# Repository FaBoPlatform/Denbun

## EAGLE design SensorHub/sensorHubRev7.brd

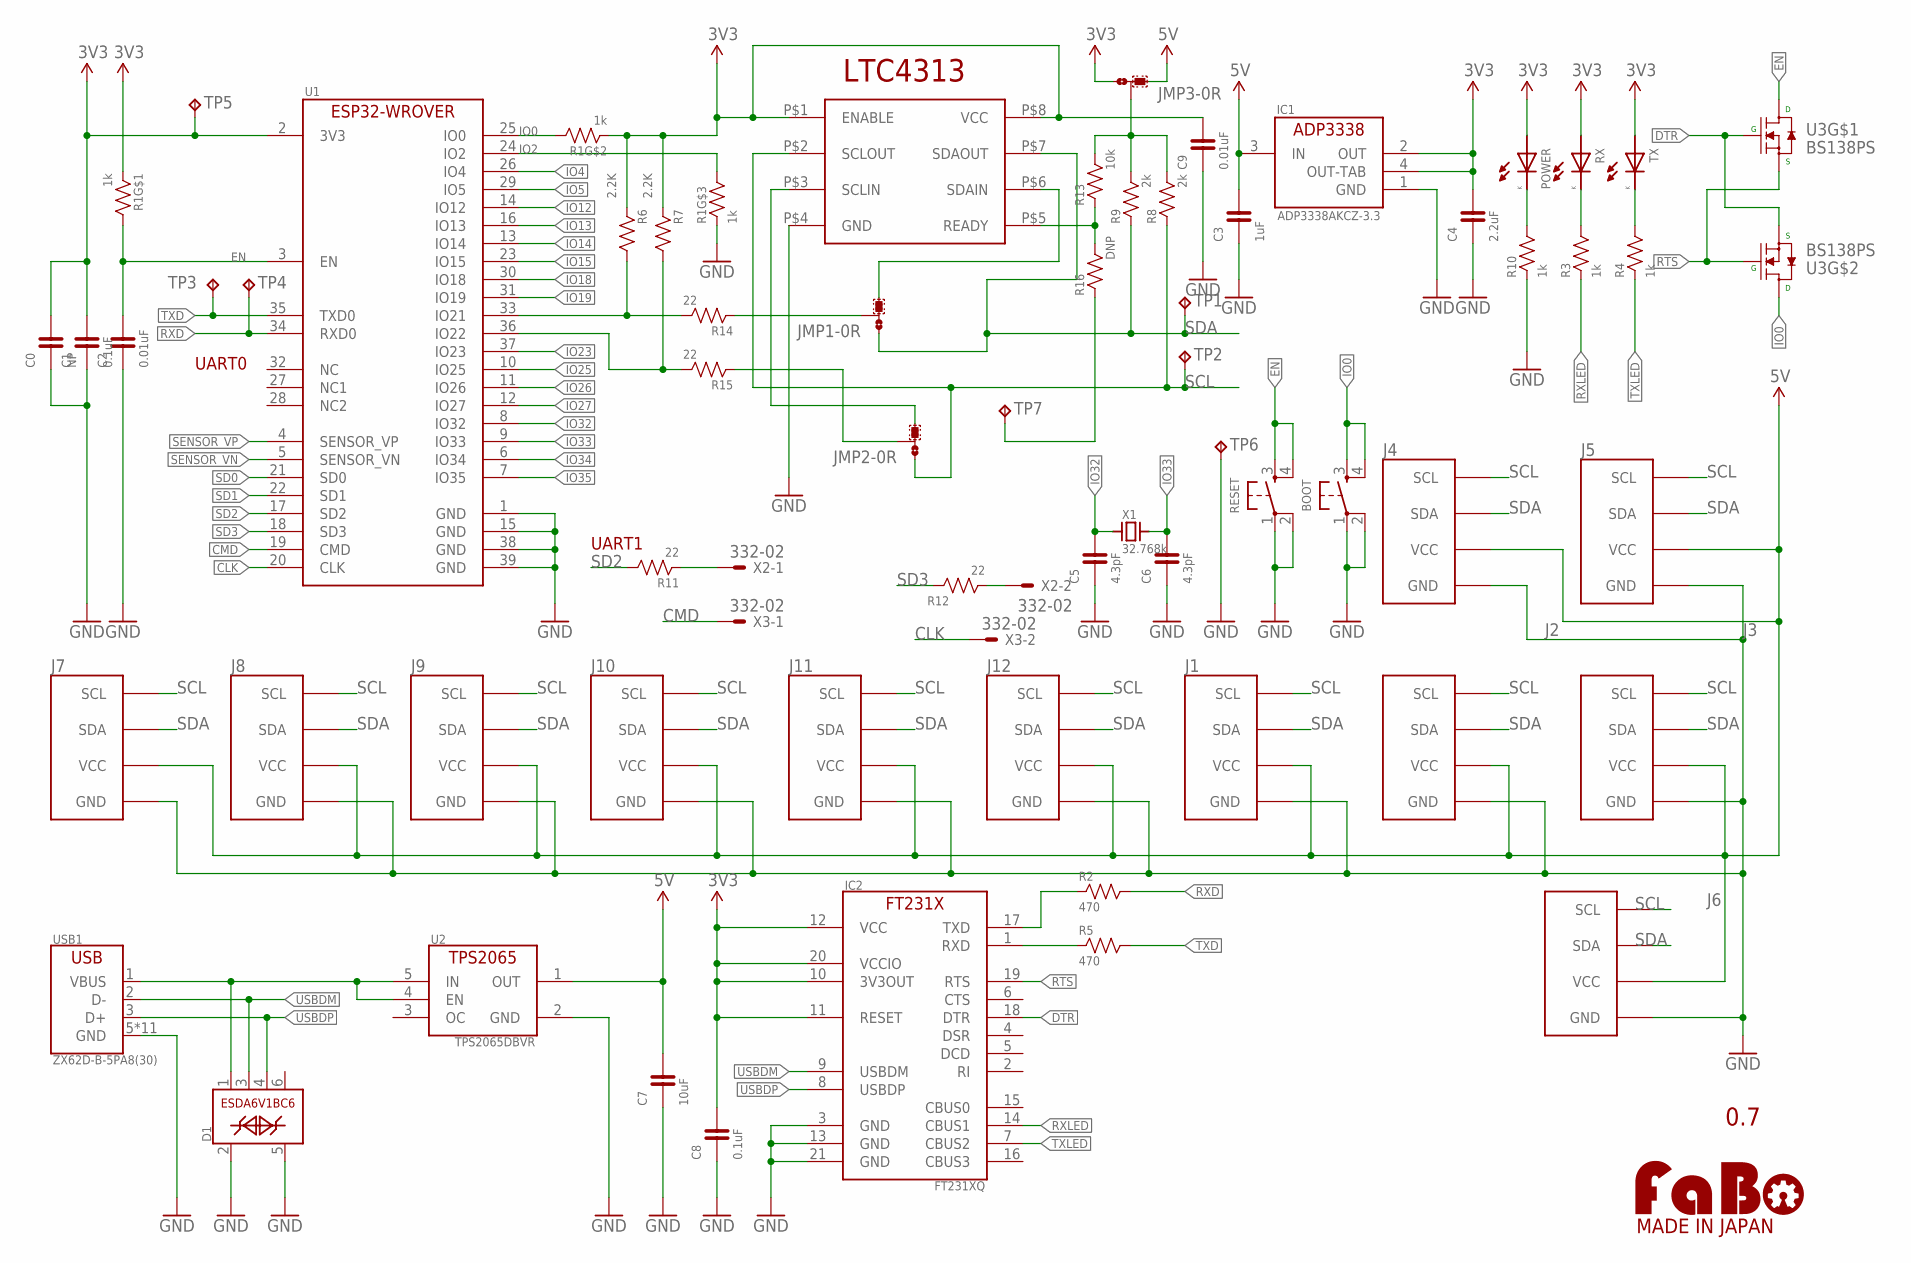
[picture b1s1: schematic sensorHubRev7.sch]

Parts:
BOOT: TACTILE-KMR2; KMR2-TACT
C0: NP; MULTIPAD0603
C1, C8: 0.1uF; EIA0603
C2, C9: 0.01uF; EIA0603
C3: 1uF; EIA0603
C4: 2.2uF; EIA0603
C5, C6: 4.3pF; EIA0603
C7: 10uF; EIA0603
D1: ESDA6V1BC6; SOT-23-6L
IC1: ADP3338AKCZ-3.3; SOT-223-KC3
IC2: FT231XQ; QFN-20
J1, J2, J3, J4, J5, J6, J7, J8, J9, J10, J11, J12: FABO_BRICK_I2C-S04B-PASK-2; FABO_BRICK_I2C_S04B-PASK-2
JMP1, JMP2: 0R-JUMPA; A0R-JMP
JMP3: 0R-JUMPB; B0R-JMP
LOGO1: LOGO_FABO-M_BOTTOM; LOGO_FABO_M_BOTTOM
POWER: LED-0603; LED_0603
R1: 1k; EXBV8V
R2, R5: 470; EIA0603
R3, R4, R10: 1k; EIA0603
R6, R7: 2.2K; EIA0603
R8, R9: 2k; EIA0603
R11, R12, R14, R15: 22; EIA0603
R13: 10k; EIA0603
R16: DNP; EIA0603
RESET: TACTILE-KMR2; KMR2-TACT
RX: LED-0603; LED_0603
TP1, TP2, TP3, TP4, TP5, TP6, TP7: TPB1,27; B1,27
TX: LED-0603; LED_0603
U1: ESP32-WROVER-B
U2: TPS2065DBVR; SOT-23-5
U3: BS138PS; SOT-363
U5: LTC4313
USB1: ZX62D-B-5PA8(30); ZX62D-B-5PA8
X1: 32.768k; ABS07
X2, X3: 332-02

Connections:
3V3: C0.2, C1.2, C4.2, C8.2, C9.2, IC1.2 (OUT), IC1.4 (OUT-TAB), IC2.10 (3V3OUT), IC2.11 (RESET), IC2.12 (VCC), IC2.20 (VCCIO), JMP3.3, POWER.A (ANODE), R1.1, R1.2 (1), R6.1, R7.1, RX.A (ANODE), TP5.TP, TX.A (ANODE), U1.2 (3V3), U5.P$1 (ENABLE), U5.P$8 (VCC)
5V: C3.2, C7.2, IC1.3 (IN), J1.VCC, J2.VCC, J3.VCC, J4.VCC, J5.VCC, J6.VCC, J7.VCC, J8.VCC, J9.VCC, J10.VCC, J11.VCC, J12.VCC, JMP3.1, U2.1 (OUT)
CLK: U1.20 (CLK), X3.2
CMD: U1.19 (CMD), X3.1
DTR: IC2.18 (DTR), U3.2 (G), U3.4 (S)
EN: C2.2, R1.8 (2), RESET.3, RESET.4, U1.3 (EN), U3.6 (D)
GND: BOOT.1, BOOT.2, C0.1, C1.1, C2.1, C3.1, C4.1, C5.1, C6.1, C7.1, C8.1, C9.1, D1.2, D1.5, IC1.1 (GND), IC2.3 (GND), IC2.13 (GND), IC2.21 (GND), J1.GND, J2.GND, J3.GND, J4.GND, J5.GND, J6.GND, J7.GND, J8.GND, J9.GND, J10.GND, J11.GND, J12.GND, R1.3 (1), R10.1, RESET.1, RESET.2, TP6.TP, U1.1 (GND), U1.15 (GND), U1.38 (GND), U1.39 (GND), U2.2 (GND), U5.P$4 (GND), USB1.5 (GND), USB1.B1 (GND), USB1.B2 (GND), USB1.B3 (GND), USB1.B4 (GND), USB1.T1 (GND), USB1.T2 (GND), USB1.T3 (GND), USB1.T4 (GND), USB1.T5 (GND), USB1.T6 (GND)
IO0: BOOT.3, BOOT.4, R1.7 (2), U1.25 (IO0), U3.3 (D)
IO2: R1.6 (2), U1.24 (IO2)
IO4: U1.26 (IO4)
IO5: U1.29 (IO5)
IO12: U1.14 (IO12)
IO13: U1.16 (IO13)
IO14: U1.13 (IO14)
IO15: U1.23 (IO15)
IO18: U1.30 (IO18)
IO19: U1.31 (IO19)
IO23: U1.37 (IO23)
IO25: U1.10 (IO25)
IO26: U1.11 (IO26)
IO27: U1.12 (IO27)
IO32: C5.2, U1.8 (IO32), X1.1
IO33: C6.2, U1.9 (IO33), X1.2
IO34: U1.6 (IO34)
IO35: U1.7 (IO35)
LED1K: POWER.K (CATHODE), R10.2
LED2K1: R3.2, RX.K (CATHODE)
LED2K2: R4.2, TX.K (CATHODE)
unnamed: IC2.1 (RXD), R5.1
unnamed: R11.1, X2.1
unnamed: IC2.17 (TXD), R2.1
unnamed: R12.1, X2.2
unnamed: JMP1.3, U5.P$6 (SDAIN)
unnamed: JMP2.3, U5.P$3 (SCLIN)
unnamed: R13.1, R16.2, U5.P$5 (READY)
unnamed: JMP1.2, R14.1
unnamed: JMP2.2, R15.1
unnamed: R6.2, R14.2, U1.33 (IO21)
unnamed: R16.1, TP7.TP
unnamed: R7.2, R15.2, U1.36 (IO22)
unnamed: JMP3.2, R8.2, R9.2, R13.2
RTS: IC2.19 (RTS), U3.1 (S), U3.5 (G)
RXD: R2.2, TP4.TP, U1.34 (RXD0)
RXLED: IC2.14 (CBUS1), R3.1
SCL: J1.SCL, J2.SCL, J3.SCL, J4.SCL, J5.SCL, J6.SCL, J7.SCL, J8.SCL, J9.SCL, J10.SCL, J11.SCL, J12.SCL, JMP2.1, R8.1, TP2.TP, U5.P$2 (SCLOUT)
SD0: U1.21 (SD0)
SD1: U1.22 (SD1)
SD2: R11.2, U1.17 (SD2)
SD3: R12.2, U1.18 (SD3)
SDA: J1.SDA, J2.SDA, J3.SDA, J4.SDA, J5.SDA, J6.SDA, J7.SDA, J8.SDA, J9.SDA, J10.SDA, J11.SDA, J12.SDA, JMP1.1, R9.1, TP1.TP, U5.P$7 (SDAOUT)
SENSOR_VN: U1.5 (SENSOR_VN)
SENSOR_VP: U1.4 (SENSOR_VP)
TXD: R5.2, TP3.TP, U1.35 (TXD0)
TXLED: IC2.7 (CBUS2), R4.1
USBDM: D1.3, IC2.9 (USBDM), USB1.2 (D-)
USBDP: D1.4, IC2.8 (USBDP), USB1.3 (D+)
USBVBUS: D1.1, U2.4 (EN), U2.5 (IN), USB1.1 (VBUS)

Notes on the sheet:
0.7
UART1
UART0

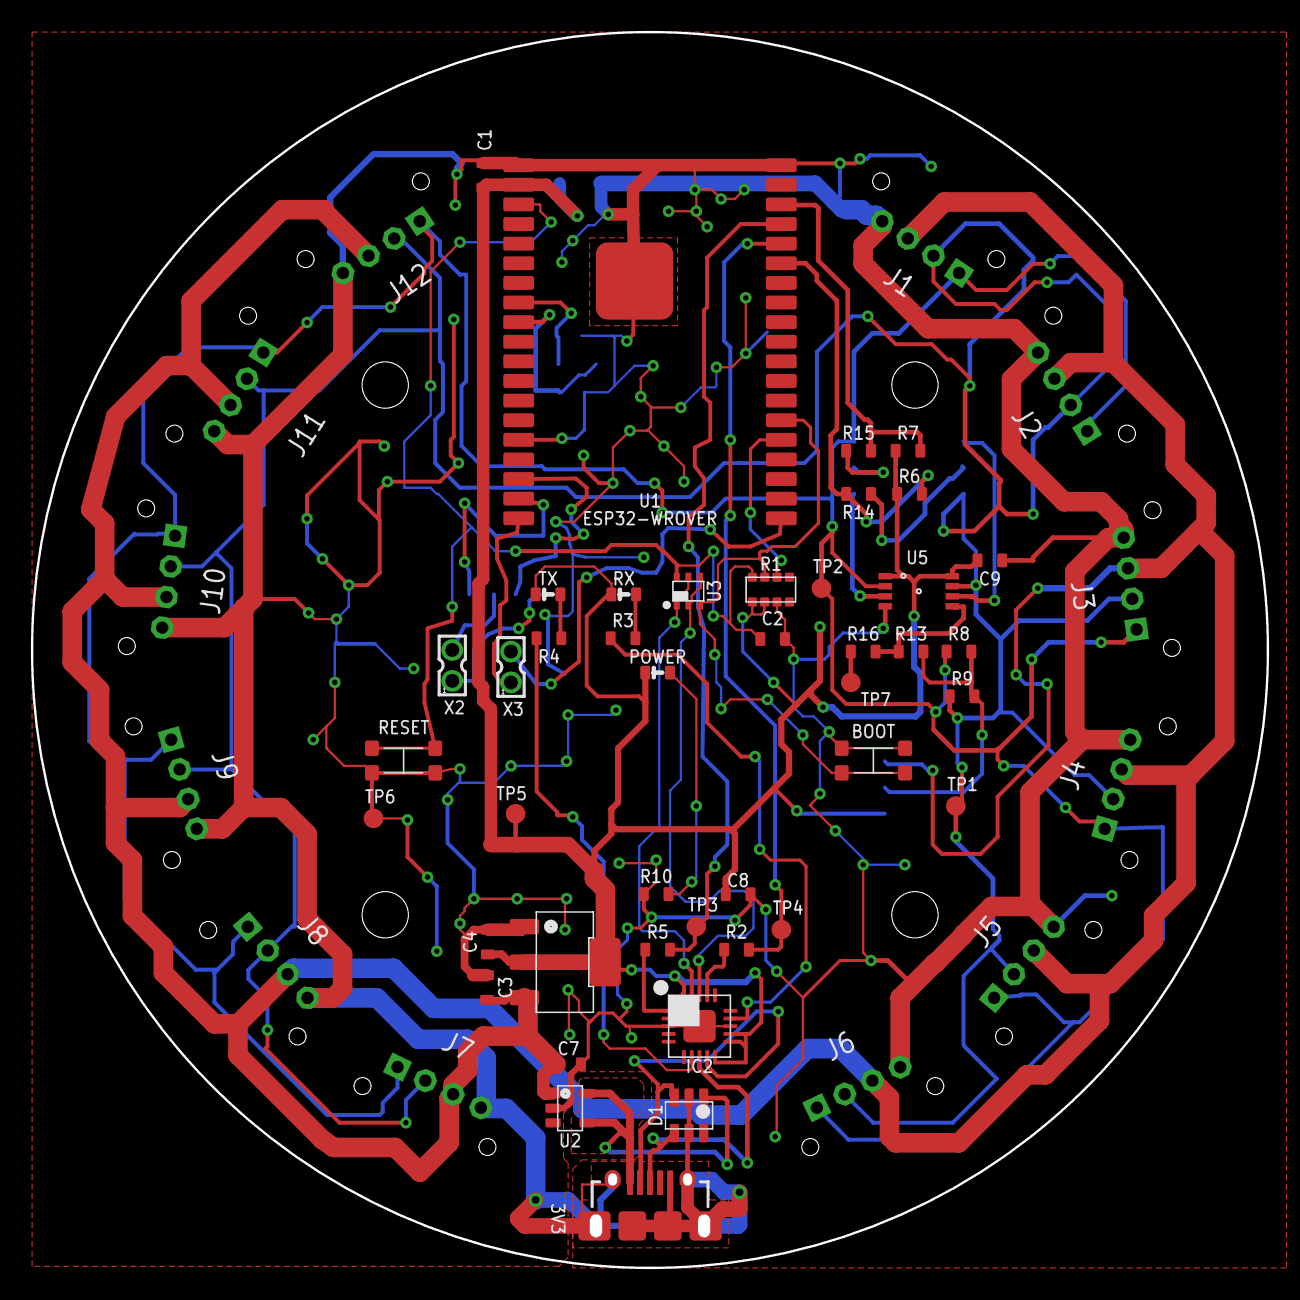
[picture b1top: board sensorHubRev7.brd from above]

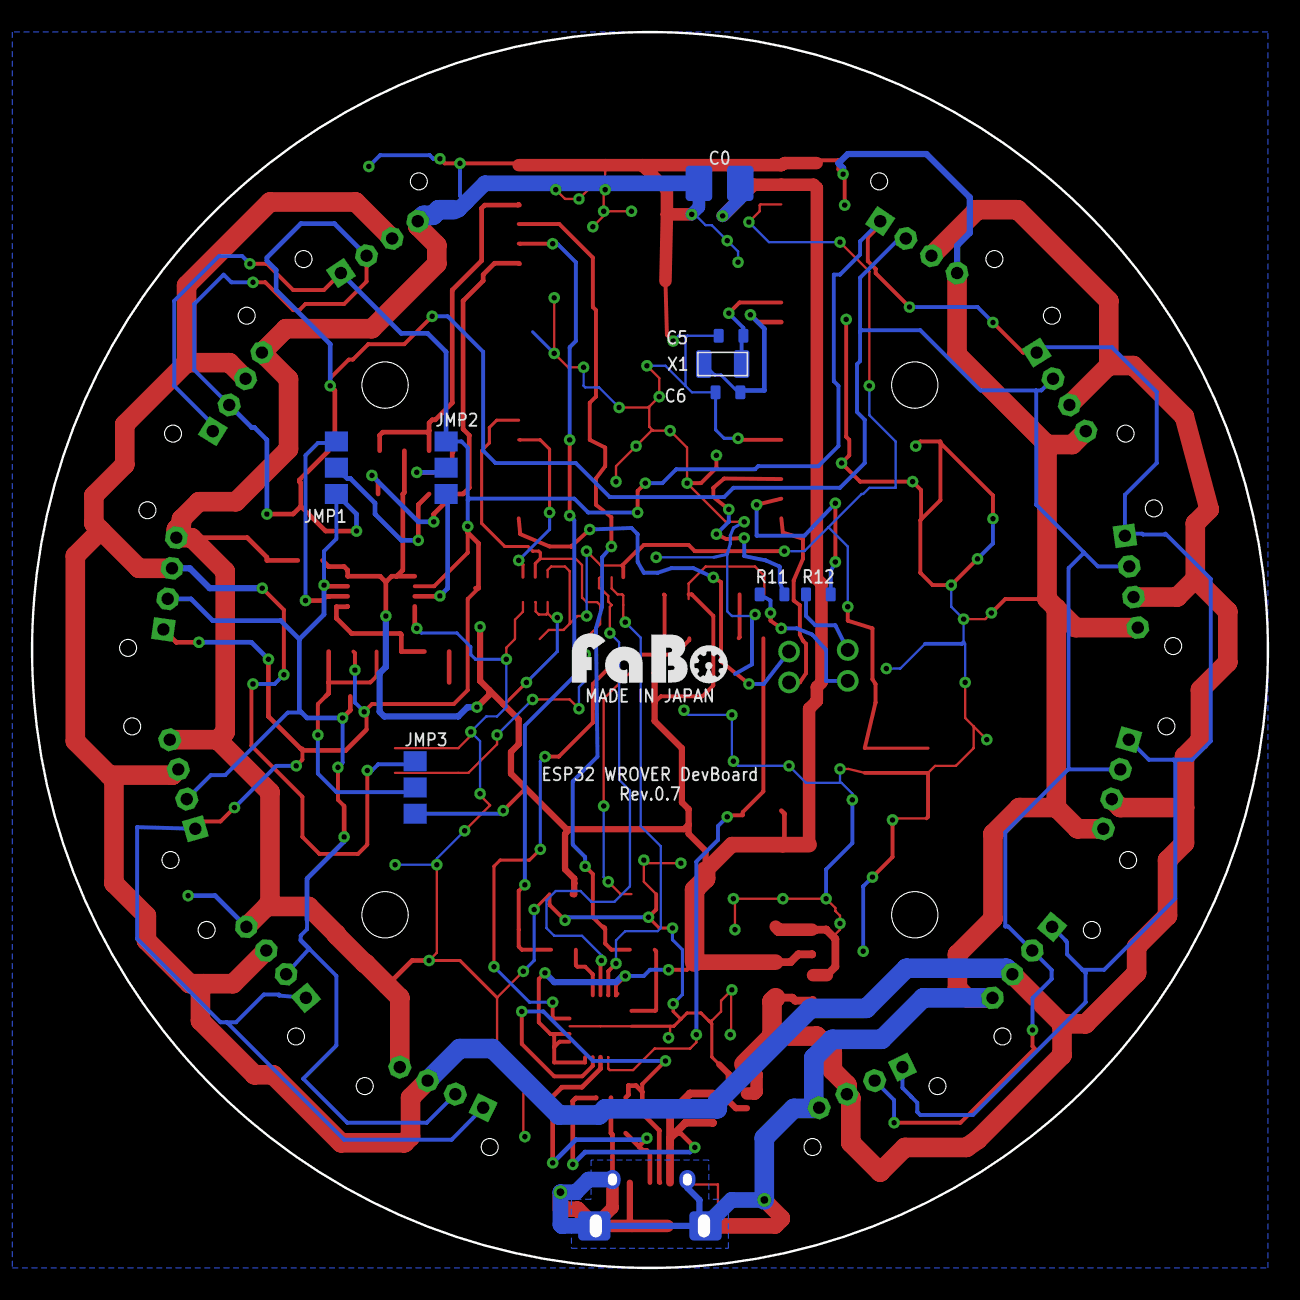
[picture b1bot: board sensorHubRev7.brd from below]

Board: 2 copper layers, 80.0 x 80.0 mm, 65 parts (9 on the bottom side), 39 nets.

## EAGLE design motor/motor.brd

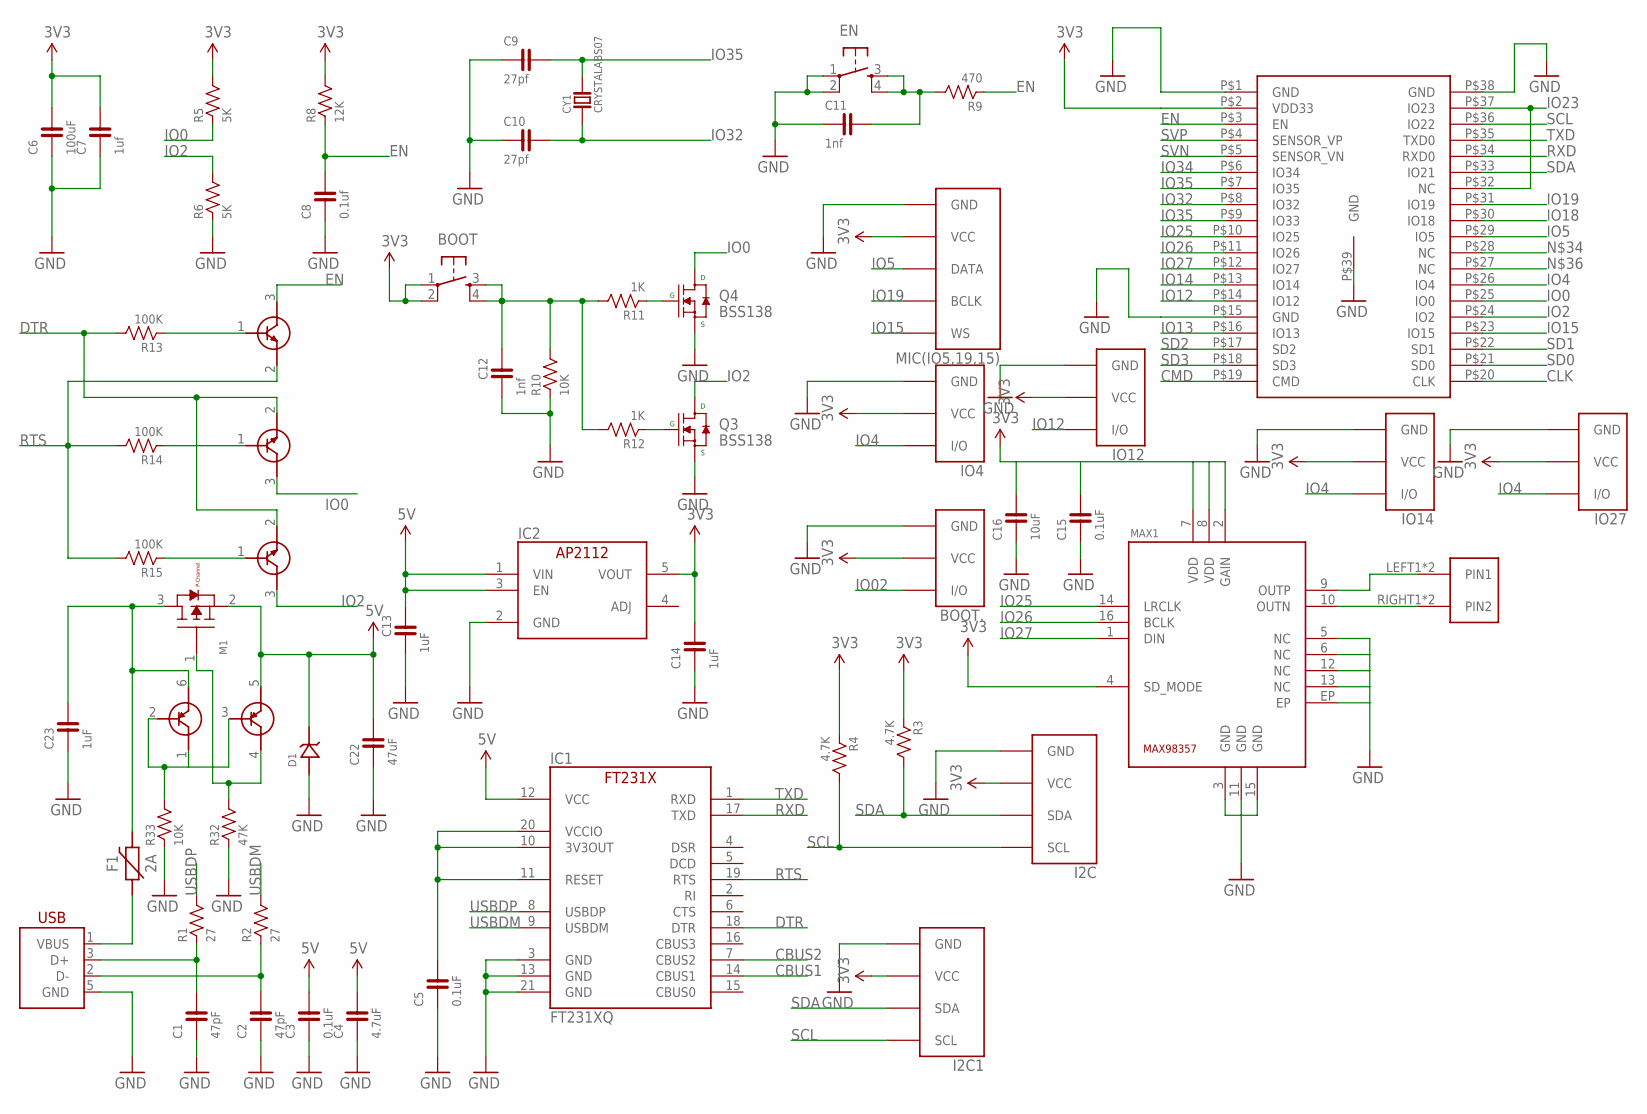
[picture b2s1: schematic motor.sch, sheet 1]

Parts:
BOOT: TACT-SWITCH-SMD_KMR2; KMR2
BOOT.: BUTTON; FABO_BRICK_3PIN_B03B-PASK-1_NAME_BOTTOM
C1, C2: 47pF; 0603-NARROW
C3, C5: 0.1uF; 0603-NARROW
C4: 4.7uF; 0603-NARROW
C6: 100uF; 1206
C7: 1uf; 0603-NARROW
C8: 0.1uf; 0603-NARROW
C9, C10: 27pf; 0603-NARROW
C11, C12: 1nf; 0603-NARROW
C13, C14: 1uF; 0603
C15: 0.1uF; 0603
C16: 10uF; 0603
C22: 47uF; 0603-NARROW
C23: 1uF; 0603-NARROW
CY1: CRYSTALABS07; ABRACOM-ABS07-32.768KHZ
D1: SMBJ5.0
EN: TACT-SWITCH-SMD_KMR2; KMR2
F1: 2A; NANOSMDC035F
I2C, I2C1: FABO_BRICK_I2C-B04B-PASK-1; FABO_BRICK_I2C_B04B-PASK-1
IC1: FT231XQ; QFN-20_FT231X
IC2: AP2112K-3.3TRG1; SOT-23-5
IO4, IO12, IO14, IO27: FABO_BRICK_3PIN-03B-PASK-1_NAME_BOTTOM; FABO_BRICK_3PIN_B03B-PASK-1_NAME_BOTTOM
M1: MOSFET-P_DMG2305UX; SOT-23
MAX1: MA-MAX98357; MAXIM-MAX98357
MIC(IO5,19,15): FABO_BRICK_I2STOP; FABO_BRICK_I2S_B05B-PARK-1
Q3, Q4: BSS138; SOT23-3
R1, R2: 27; 0603-NARROW
R3, R4: 4.7K; 0603-NARROW
R5, R6: 5K; 0603-NARROW
R8: 12K; 0603-NARROW
R9: 470; 0603-NARROW
R10, R33: 10K; 0603-NARROW
R11, R12: 1K; 0603-NARROW
R13, R14, R15: 100K; 0603-NARROW
R32: 47K; 0603-NARROW
T1, T2, T3: TRANSISTORMMBT2222; SOT-23
U$1: ESP32-WROVER
U$4: ML-1400-S1
U$6: DUAL-PNP-TRANSISTORDMMT5401; SOT-26
USB1: USB-MICRO_B_SMT_HIROSE; ZX62R-B-5P

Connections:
3V3: BOOT.1, BOOT.2, BOOT..VCC, C6.- (2), C7.2, C14.2, C15.2, C16.2, I2C.VCC, I2C1.VCC, IC2.5 (VOUT), IO4.VCC, IO12.VCC, IO14.VCC, IO27.VCC, MAX1.2 (GAIN), MAX1.4 (SD_MODE), MAX1.7 (VDD), MAX1.8 (VDD), MIC(IO5,19,15).VCC, R3.1, R4.1, R5.2, R8.2, U$1.P$2 (VDD33); also elsewhere on the board
5V: C3.2, C4.2, C13.2, C22.2, D1.ANODE, IC1.12 (VCC), IC2.1 (VIN), IC2.3 (EN), M1.2 (S), U$6.5 (E2); also elsewhere on the board
CBUS1: IC1.14 (CBUS1)
CBUS2: IC1.7 (CBUS2)
CLK: U$1.P$20 (CLK)
CMD: U$1.P$19 (CMD)
DTR: IC1.18 (DTR), R13.2, T2.2 (E), T3.2 (E)
EN: C8.2, R8.1, R9.1, T1.3 (C), U$1.P$3 (EN)
GND: BOOT..GND, C1.1, C2.1, C3.1, C4.1, C5.1, C6.+ (1), C7.1, C8.1, C9.1, C10.1, C11.1, C12.1, C13.1, C14.1, C15.1, C16.1, C22.1, C23.1, D1.CATHODE, EN.1, EN.2, I2C.GND, I2C1.GND, IC1.3 (GND), IC1.13 (GND), IC1.21 (GND), IC2.2 (GND), IO4.GND, IO12.GND, IO14.GND, IO27.GND, MAX1.3 (GND), MAX1.5 (NC), MAX1.6 (NC), MAX1.11 (GND), MAX1.12 (NC), MAX1.13 (NC), MAX1.15 (GND), MAX1.EP, MIC(IO5,19,15).GND, Q3.2 (S), Q4.2 (S), R6.1, R10.1, R32.1, R33.1, U$1.P$1 (GND), U$1.P$15 (GND), U$1.P$38 (GND), U$1.P$39 (GND), USB1.5 (GND); also elsewhere on the board
IO0: Q4.3 (D), R5.1, T2.3 (C), U$1.P$25 (IO0)
IO2: Q3.3 (D), R6.2, T3.3 (C), U$1.P$24 (IO2)
IO02: BOOT..I/O
IO4: IO4.I/O, IO14.I/O, IO27.I/O, U$1.P$26 (IO4)
IO5: MIC(IO5,19,15).DATA, U$1.P$29 (IO5)
IO12: IO12.I/O, U$1.P$14 (IO12)
IO13: U$1.P$16 (IO13)
IO14: U$1.P$13 (IO14)
IO15: MIC(IO5,19,15).WS, U$1.P$23 (IO15)
IO18: U$1.P$30 (IO18)
IO19: MIC(IO5,19,15).BCLK, U$1.P$31 (IO19)
IO23: U$1.P$32 (NC), U$1.P$37 (IO23)
IO25: MAX1.14 (LRCLK), U$1.P$10 (IO25)
IO26: MAX1.16 (BCLK), U$1.P$11 (IO26)
IO27: MAX1.1 (DIN), U$1.P$12 (IO27)
IO32: C10.2, CY1.P$1, U$1.P$8 (IO32)
IO34: U$1.P$6 (IO34); also elsewhere on the board
IO35: C9.2, CY1.P$2, U$1.P$7 (IO35), U$1.P$9 (IO33); also elsewhere on the board
unnamed: R13.1, T1.1 (B)
unnamed: R14.1, T2.1 (B)
unnamed: C2.2, R2.1, USB1.2 (D-)
unnamed: C1.2, R1.1, USB1.3 (D+)
unnamed: C11.2, EN.3, EN.4, R9.2
unnamed: BOOT.3, BOOT.4, C12.2, R10.2, R11.2, R12.2
unnamed: C5.2, IC1.10 (3V3OUT), IC1.11 (RESET), IC1.20 (VCCIO)
unnamed: R15.1, T3.1 (B)
unnamed: MAX1.10 (OUTN), U$4.RIGHT1 (PIN2), U$4.RIGHT2 (PIN2)
unnamed: MAX1.9 (OUTP), U$4.LEFT1 (PIN1), U$4.LEFT2 (PIN1)
unnamed: Q4.1 (G), R11.1
unnamed: Q3.1 (G), R12.1
unnamed: C23.2, F1.2, M1.3 (D), U$6.6 (E1)
unnamed: M1.1 (G), R32.2, U$6.4 (C2)
unnamed: R33.2, U$6.1 (C1), U$6.2 (B1), U$6.3 (B2)
RTS: IC1.19 (RTS), R14.2, R15.2, T1.2 (E)
RXD: IC1.17 (TXD), U$1.P$34 (RXD0)
SCL: I2C.SCL, I2C1.SCL, R4.2, U$1.P$36 (IO22); also elsewhere on the board
SD0: U$1.P$21 (SD0)
SD1: U$1.P$22 (SD1)
SD2: U$1.P$17 (SD2)
SD3: U$1.P$18 (SD3)
SDA: I2C.SDA, I2C1.SDA, R3.2, U$1.P$33 (IO21); also elsewhere on the board
SVN: U$1.P$5 (SENSOR_VN)
SVP: U$1.P$4 (SENSOR_VP)
TXD: IC1.1 (RXD), U$1.P$35 (TXD0)
USBDM: IC1.9 (USBDM), R2.2
USBDP: IC1.8 (USBDP), R1.2
VBUS: F1.1, USB1.1 (VBUS)

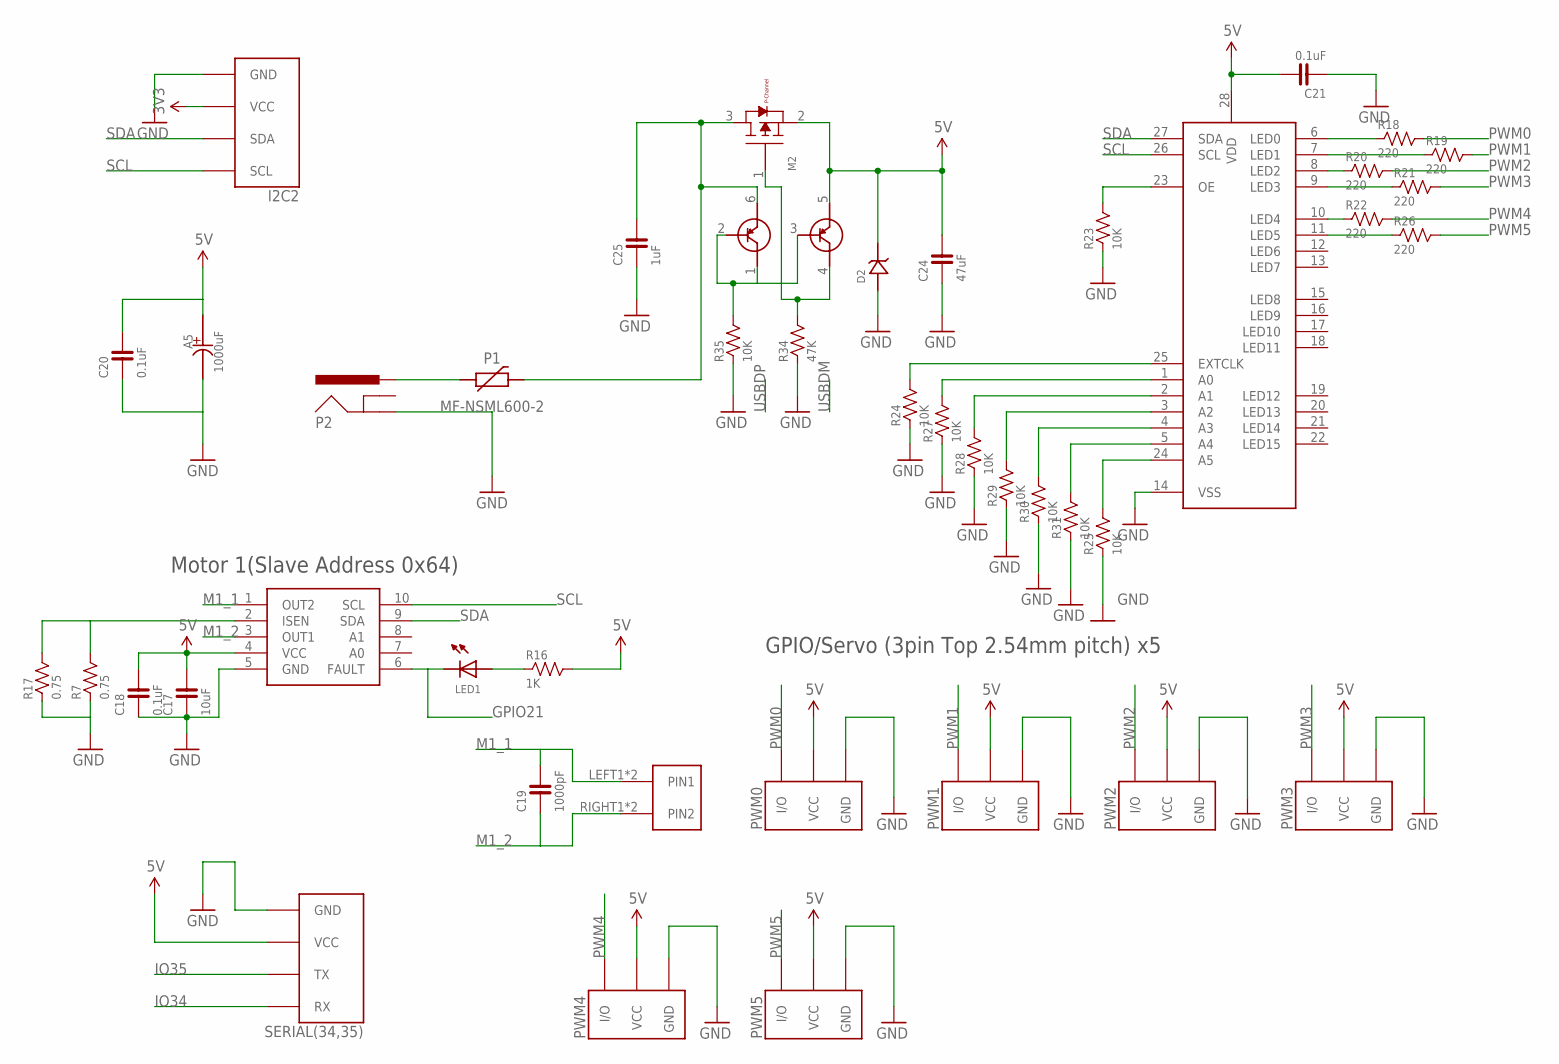
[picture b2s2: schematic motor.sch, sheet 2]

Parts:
A5: 1000uF; D12.5
C17: 10uF; 0603
C18, C20, C21: 0.1uF; 0603
C19: 1000pF; 0603
C24: 47uF; 0603-NARROW
C25: 1uF; 0603-NARROW
D2: SMBJ5.0
I2C2: FABO_BRICK_I2C-B04B-PASK-1; FABO_BRICK_I2C_B04B-PASK-1
LED1: LED-0603; 0603
M2: MOSFET-P_DMG2305UX; SOT-23
P1: MF-NSML600-2; 1206
P2: DC-JACKM04339A0; M04339A0
PWM0, PWM1, PWM2, PWM3, PWM4, PWM5: FABO_BRICK_3PIN-HEADER; FABO_BRICK_3PIN_HEADER
R7, R17: 0.75; 0603
R16: 1K; 0603
R18, R19, R20, R21, R22, R26: 220; 0603
R23, R24, R25, R27, R28, R29, R30, R31: 10K; 0603
R34: 47K; 0603-NARROW
R35: 10K; 0603-NARROW
SERIAL(34,35): FABO_BRICK_SERIAL-B04B-PASK-1; FABO_BRICK_SERIAL_B04B-PASK-1
U$7: DUAL-PNP-TRANSISTORDMMT5401; SOT-26
U$8: DRV8830
U$9: PCA9685
U$12: ML-1400-S1

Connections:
3V3: I2C2.VCC; also elsewhere on the board
5V: A5.+, C17.2, C18.2, C20.2, C21.2, C24.2, D2.ANODE, M2.2 (S), PWM0.VCC, PWM1.VCC, PWM2.VCC, PWM3.VCC, PWM4.VCC, PWM5.VCC, R16.2, SERIAL(34,35).VCC, U$7.5 (E2), U$8.4 (VCC), U$9.28 (VDD); also elsewhere on the board
GND: A5.-, C17.1, C18.1, C20.1, C21.1, C24.1, C25.1, D2.CATHODE, I2C2.GND, P2.GND, PWM0.GND, PWM1.GND, PWM2.GND, PWM3.GND, PWM4.GND, PWM5.GND, R7.1, R17.1, R23.1, R24.1, R25.1, R27.1, R28.1, R29.1, R30.1, R31.1, R34.1, R35.1, SERIAL(34,35).GND, U$8.5 (GND), U$9.14 (VSS); also elsewhere on the board
GPIO21: LED1.CATHODE, U$8.6 (FAULT)
IO34: SERIAL(34,35).RX; also elsewhere on the board
IO35: SERIAL(34,35).TX; also elsewhere on the board
LED0: R18.1, U$9.6 (LED0)
LED1: R19.1, U$9.7 (LED1)
LED2: R20.1, U$9.8 (LED2)
LED3: R21.1, U$9.9 (LED3)
LED4: R22.1, U$9.10 (LED4)
LED5: R26.1, U$9.11 (LED5)
M1_1: C19.2, U$8.1 (OUT2), U$12.LEFT1 (PIN1), U$12.LEFT2 (PIN1)
M1_2: C19.1, U$8.3 (OUT1), U$12.RIGHT1 (PIN2), U$12.RIGHT2 (PIN2)
unnamed: R7.2, R17.2, U$8.2 (ISEN)
unnamed: LED1.ANODE, R16.1
unnamed: P1.P$1 (1), P2.VCC (PWR)
unnamed: R23.2, U$9.23 (OE)
unnamed: R24.2, U$9.25 (EXTCLK)
unnamed: R27.2, U$9.1 (A0)
unnamed: R28.2, U$9.2 (A1)
unnamed: R29.2, U$9.3 (A2)
unnamed: R30.2, U$9.4 (A3)
unnamed: R31.2, U$9.5 (A4)
unnamed: R25.2, U$9.24 (A5)
unnamed: C25.2, M2.3 (D), P1.P$2 (2), U$7.6 (E1)
unnamed: M2.1 (G), R34.2, U$7.4 (C2)
unnamed: R35.2, U$7.1 (C1), U$7.2 (B1), U$7.3 (B2)
PWM0: PWM0.I/O, R18.2
PWM1: PWM1.I/O, R19.2
PWM2: PWM2.I/O, R20.2
PWM3: PWM3.I/O, R21.2
PWM4: PWM4.I/O, R22.2
PWM5: PWM5.I/O, R26.2
SCL: I2C2.SCL, U$8.10 (SCL), U$9.26 (SCL); also elsewhere on the board
SDA: I2C2.SDA, U$8.9 (SDA), U$9.27 (SDA); also elsewhere on the board

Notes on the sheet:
Motor 1(Slave Address 0x64)
GPIO/Servo (3pin Top 2.54mm pitch) x5

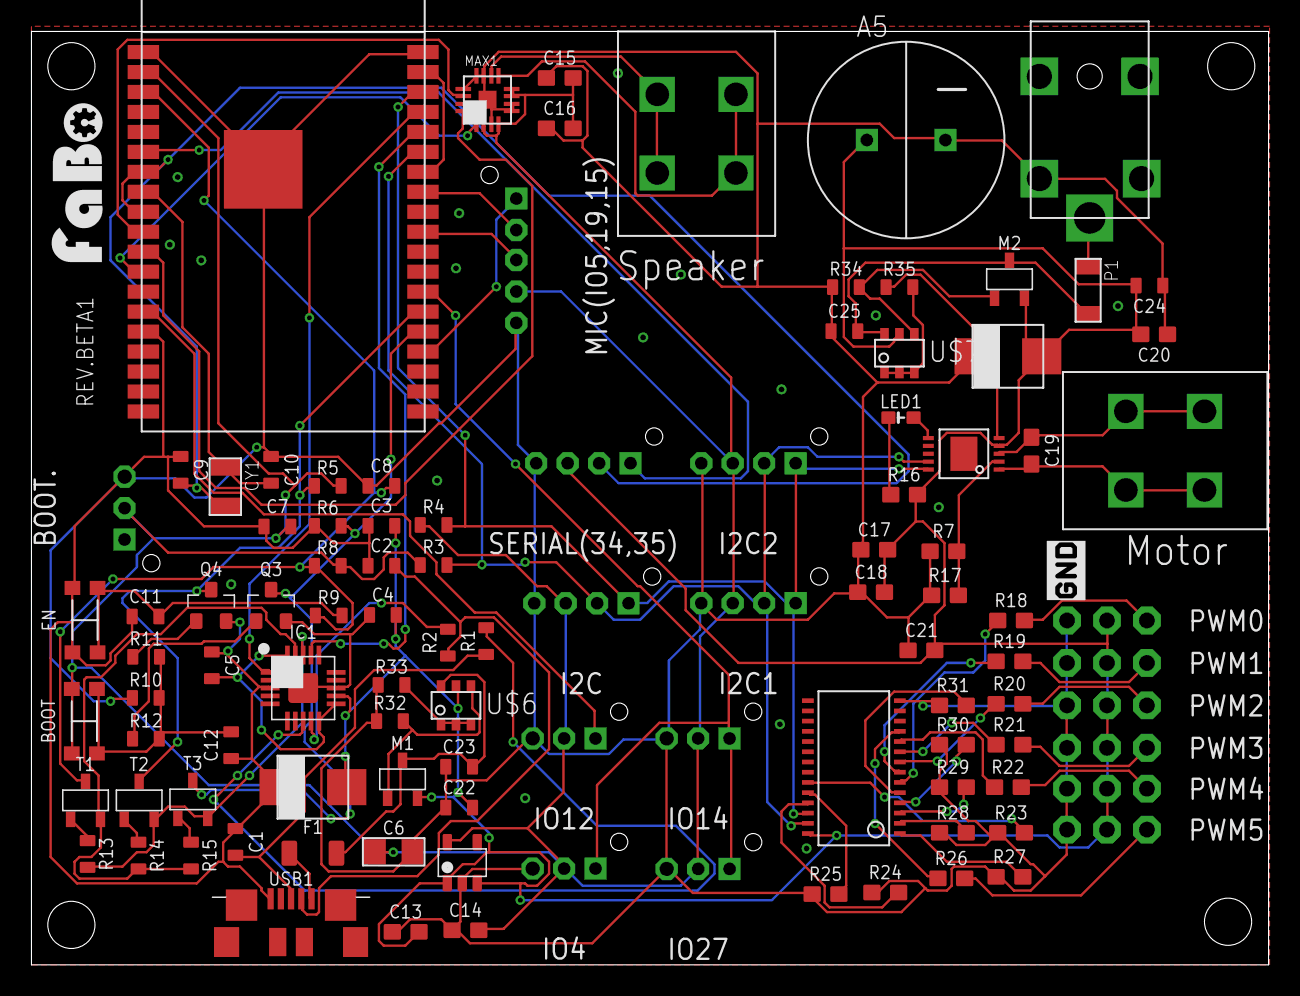
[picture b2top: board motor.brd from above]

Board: 2 copper layers, 78.7 x 59.4 mm, 106 parts (0 on the bottom side), 71 nets.

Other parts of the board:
U$5: LOGO_FABO_MS
U$19: LOGO_SILK_GND

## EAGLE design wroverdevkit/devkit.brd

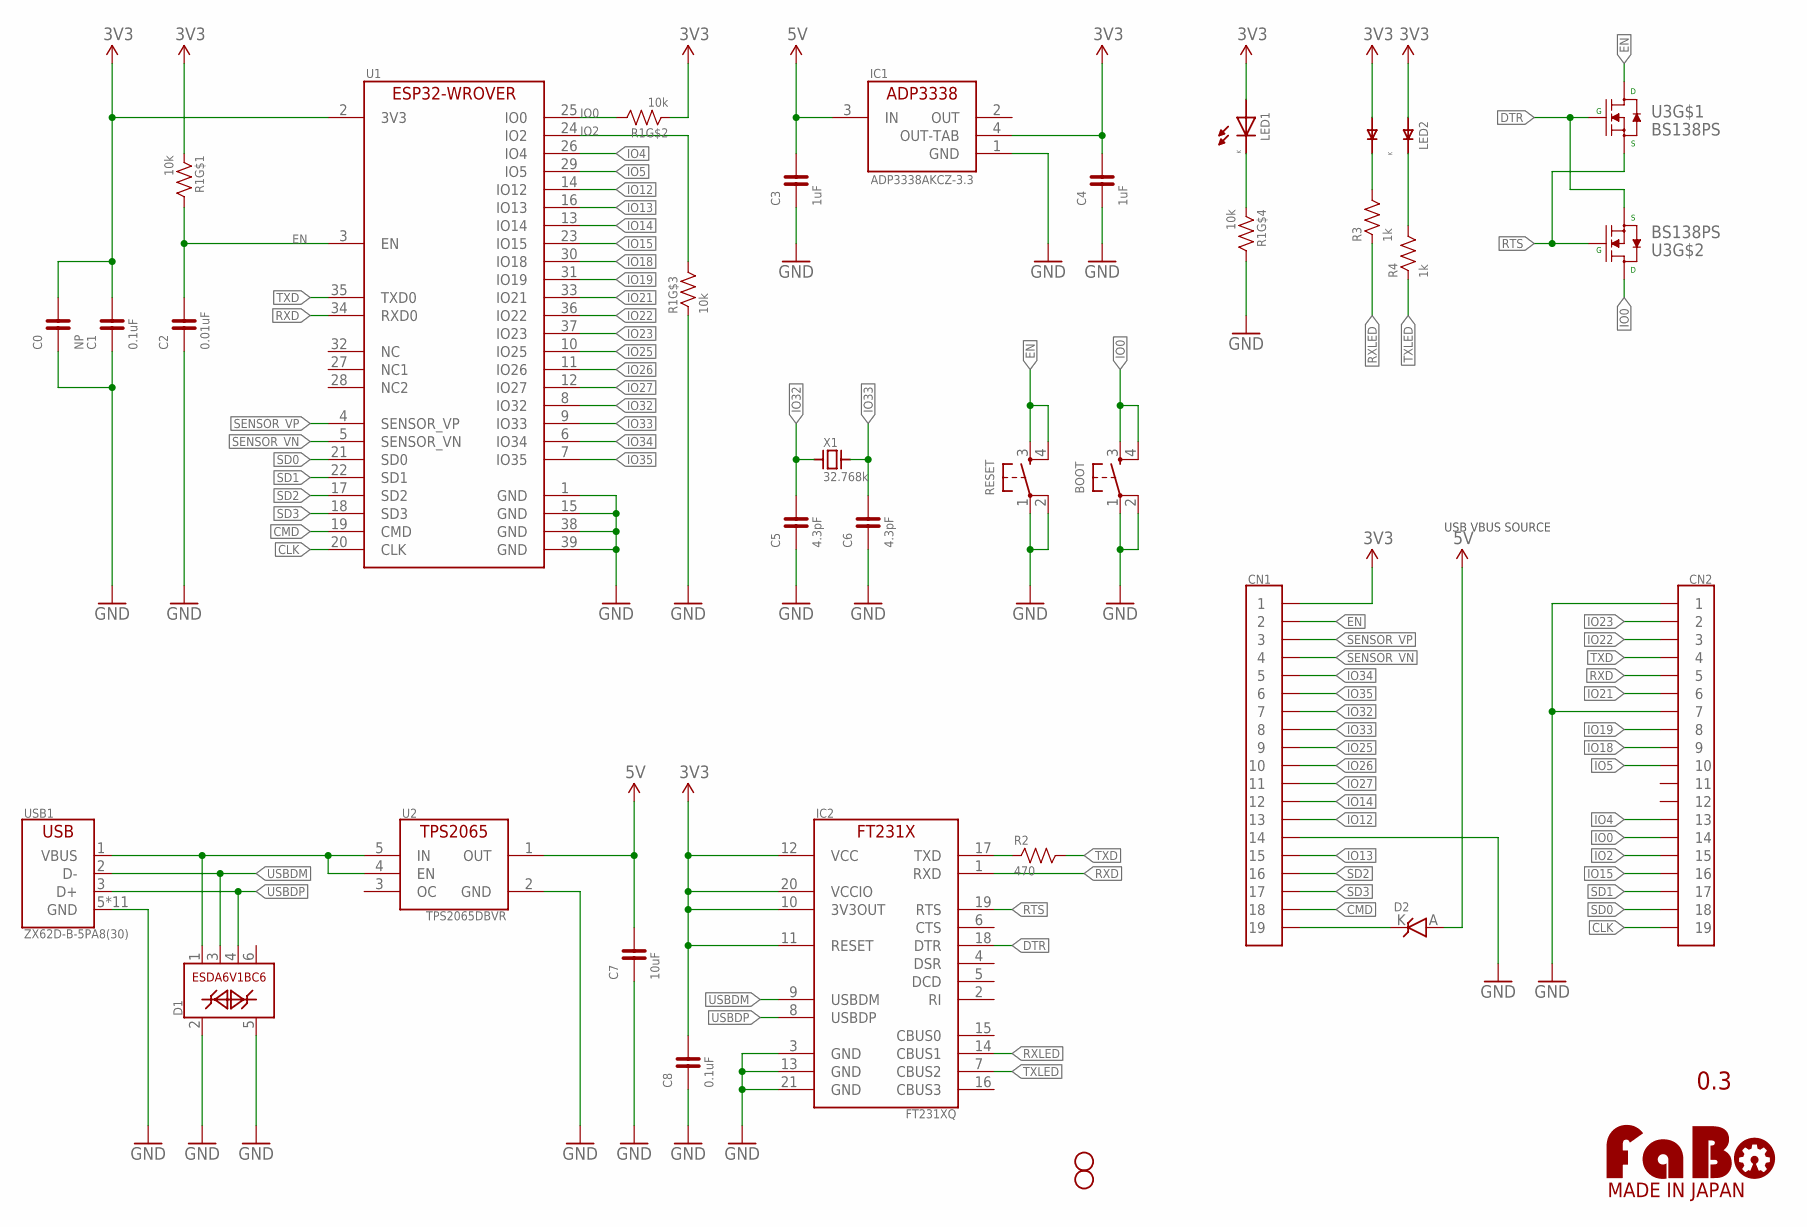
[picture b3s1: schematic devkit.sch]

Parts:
BOOT: TACTILE-KMR2; KMR2-TACT
C0: NP; MULTIPAD0603
C1, C8: 0.1uF; EIA0603
C2: 0.01uF; EIA0603
C3, C4: 1uF; EIA0603
C5, C6: 4.3pF; EIA0603
C7: 10uF; EIA0603
CN1, CN2: PIN_1X19
D1: ESDA6V1BC6; SOT-23-6L
D2: DIODE_SCHOTTKY-RB161MM-20; SOD-123FL_RB161MM-20
FID1, FID2: FIDUCIAL-TOP; FIDUCIAL_15_TOP
IC1: ADP3338AKCZ-3.3; SOT-223-KC3
IC2: FT231XQ; QFN-20
LED1: LED-0603; LED_0603
LED2: HSMF-C16X
LOGO1: LOGO_FABO-M_BOTTOM; LOGO_FABO_M_BOTTOM
R1: 10k; EXBV8V
R2: 470; EIA0603
R3, R4: 1k; EIA0603
RESET: TACTILE-KMR2; KMR2-TACT
U1: ESP32-WROVER-B
U2: TPS2065DBVR; SOT-23-5
U3: BS138PS; SOT-363
USB1: ZX62D-B-5PA8(30); ZX62D-B-5PA8
X1: 32.768k; ABS07

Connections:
3V3: C0.2, C1.2, C4.2, C8.2, CN1.1, IC1.4 (OUT-TAB), IC2.10 (3V3OUT), IC2.11 (RESET), IC2.12 (VCC), IC2.20 (VCCIO), LED1.A (ANODE), LED2.1 (A1), LED2.2 (A2), R1.1, R1.2 (1), U1.2 (3V3)
5V: C3.2, C7.2, D2.A, IC1.3 (IN), U2.1 (OUT)
CLK: CN2.19, U1.20 (CLK)
CMD: CN1.18, U1.19 (CMD)
DTR: IC2.18 (DTR), U3.2 (G), U3.4 (S)
EN: C2.2, CN1.2, R1.8 (2), RESET.3, RESET.4, U1.3 (EN), U3.6 (D)
GND: BOOT.1, BOOT.2, C0.1, C1.1, C2.1, C3.1, C4.1, C5.1, C6.1, C7.1, C8.1, CN1.14, CN2.1, CN2.7, D1.2, D1.5, IC1.1 (GND), IC2.3 (GND), IC2.13 (GND), IC2.21 (GND), R1.3 (1), R1.5 (2), RESET.1, RESET.2, U1.1 (GND), U1.15 (GND), U1.38 (GND), U1.39 (GND), U2.2 (GND), USB1.5 (GND), USB1.B1 (GND), USB1.B2 (GND), USB1.B3 (GND), USB1.B4 (GND), USB1.T1 (GND), USB1.T2 (GND), USB1.T3 (GND), USB1.T4 (GND), USB1.T5 (GND), USB1.T6 (GND)
IO0: BOOT.3, BOOT.4, CN2.14, R1.7 (2), U1.25 (IO0), U3.3 (D)
IO2: CN2.15, R1.6 (2), U1.24 (IO2)
IO4: CN2.13, U1.26 (IO4)
IO5: CN2.10, U1.29 (IO5)
IO12: CN1.13, U1.14 (IO12)
IO13: CN1.15, U1.16 (IO13)
IO14: CN1.12, U1.13 (IO14)
IO15: CN2.16, U1.23 (IO15)
IO18: CN2.9, U1.30 (IO18)
IO19: CN2.8, U1.31 (IO19)
IO21: CN2.6, U1.33 (IO21)
IO22: CN2.3, U1.36 (IO22)
IO23: CN2.2, U1.37 (IO23)
IO25: CN1.9, U1.10 (IO25)
IO26: CN1.10, U1.11 (IO26)
IO27: CN1.11, U1.12 (IO27)
IO32: C5.2, CN1.7, U1.8 (IO32), X1.1
IO33: C6.2, CN1.8, U1.9 (IO33), X1.2
IO34: CN1.5, U1.6 (IO34)
IO35: CN1.6, U1.7 (IO35)
LED1K: LED1.K (CATHODE), R1.4 (1)
LED2K1: LED2.4 (K2), R3.2
LED2K2: LED2.3 (K1), R4.2
OUT5V: CN1.19, D2.K
RTS: IC2.19 (RTS), U3.1 (S), U3.5 (G)
RXD: CN2.5, IC2.1 (RXD), U1.34 (RXD0)
RXLED: IC2.14 (CBUS1), R3.1
SD0: CN2.18, U1.21 (SD0)
SD1: CN2.17, U1.22 (SD1)
SD2: CN1.16, U1.17 (SD2)
SD3: CN1.17, U1.18 (SD3)
SENSOR_VN: CN1.4, U1.5 (SENSOR_VN)
SENSOR_VP: CN1.3, U1.4 (SENSOR_VP)
TXD: CN2.4, R2.2, U1.35 (TXD0)
TXLED: IC2.7 (CBUS2), R4.1
TXPIN: IC2.17 (TXD), R2.1
USBDM: D1.3, IC2.9 (USBDM), USB1.2 (D-)
USBDP: D1.4, IC2.8 (USBDP), USB1.3 (D+)
USBVBUS: D1.1, U2.4 (EN), U2.5 (IN), USB1.1 (VBUS)

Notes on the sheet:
0.3
USB VBUS SOURCE

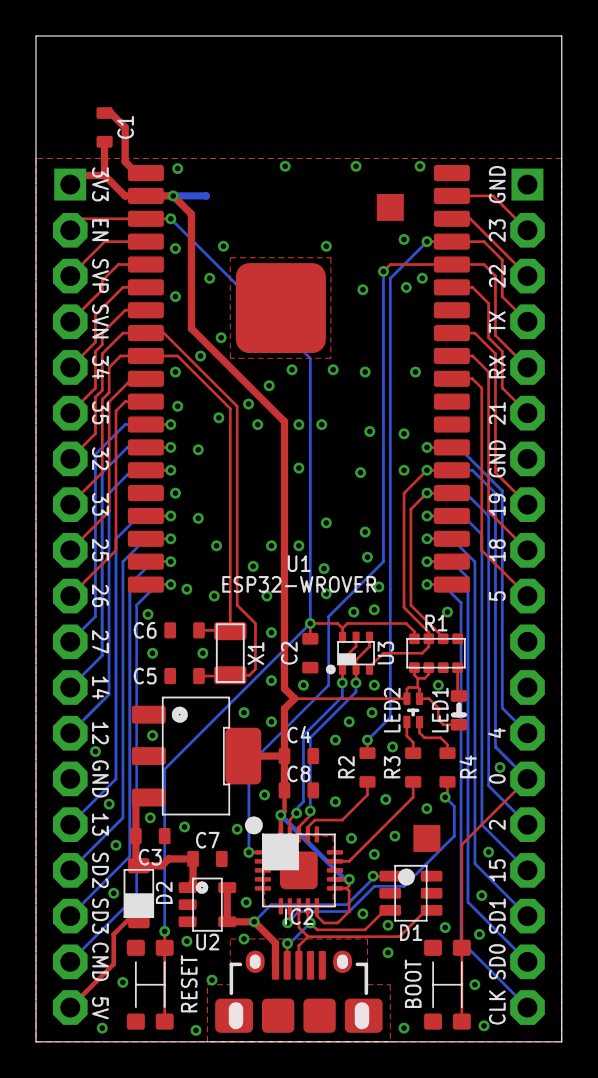
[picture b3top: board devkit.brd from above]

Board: 2 copper layers, 29.2 x 55.9 mm, 31 parts (1 on the bottom side), 46 nets.

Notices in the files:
parts and their libraries:
FaBo-Template: Released under the Creative Commons Attribution-ShareAlike 4.0 License
https://creativecommons.org/licenses/by-sa/4.0
component: Released under the Creative Commons
